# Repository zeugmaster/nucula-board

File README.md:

# Nucula Board

An ESP32-C3 hardware prototype with USB-C, battery charging, PN7160 NFC,
an SSD1309 OLED interface, and a detachable I²C keyboard section.

**Current production files: [production-2026-10-09-package.zip](manufacturing/production-2026-10-09-package.zip).**
The current board preserves rev-A NFC copper, matching values and placement,
including its small vias, filled/capped fabrication and JLC04161H-3313 stackup.
It retains the corrected display mapping, USB isolation redesign, MINI-1 module,
six M2 holes, inward battery connector and rounded cable notch.
[Production instructions and validation scope](docs/production-release.md).
All previous October packages are superseded for this order. Revised USB/display
operation and the new NFC substitutes still require bench validation. See the
stock-substitution qualification included in this release.

## Open the design

Clone this repository and open `nucula-v2.kicad_pro` in **KiCad 10** with its
standard symbol, footprint and 3D libraries installed. Project-specific libraries
use relative paths. The project filenames retain the hardware revision name
`nucula-v2`; the GitHub repository is `nucula-board`.

```sh
git clone https://github.com/zeugmaster/nucula-board.git
cd nucula-board
python3 tools/check_schematic.py
```

The check requires Python 3 and KiCad CLI. See [validation and repository
notes](docs/publication.md) for other checks, dependencies and historical inputs.

## Hardware and documentation

The five-sheet schematic contains the ESP32-C3-MINI-1-H4X, native USB-C data,
a 100 mA single-cell Li-ion charger with JST-SH connector, USB/battery supply
selection, a 3.31 V buck rail, and boot/reset/voltage supervision. It is adapted
from Olimex ESP32-C3-DevKit-Lipo **revision C**. It now includes the PN7160 NFC
controller and antenna matching tree, SSD1309 OLED glass driver/boost supply,
and a detachable PCF8574T keyboard section. The four-layer PCB is placed and
routed, with all components on top and the NFC circuitry inside the coil.

- [M2 mounting-hole positions, clearances and validation](docs/mounting-holes.md)
- [MINI-1 compatibility, pin map, antenna fit and firmware requirements](docs/esp32-mini.md)
- [Completed PCB layout, layer drawings and validation](docs/pcb-layout.md)
- [Rev-A display correction, backfeed investigation and measurements](docs/bringup/rev-b-display-and-usb.md)
- [Rev-A bench procedure with enlarged probe-pad map (PDF)](docs/bringup/rev-A-usb-bench-guide.pdf)
- [Routing repair, before/after comparison and geometry audit](docs/routing-review.md)
- [Standard manufacturing package and order settings](docs/manufacturing-release.md)
- [Current prototype manufacturing ZIP](manufacturing/production-2026-10-09-package.zip)
- [Side-entry battery connector selection, polarity and assembly instructions](docs/battery-connector.md)
- [Circuit simulation screening, findings and model limits](docs/simulation/README.md)
- [Schematic PDF](docs/schematic.pdf)
- [Design choices, datasheets and outstanding hardware limits](docs/power-design.md)
- [NFC, OLED, I²C pin map and breakaway keyboard design](docs/peripherals-design.md)
- [35 mm keyboard breakaway geometry and separation instructions](docs/keyboard-breakaway.md)
- [40 mm NFC coil, calculated matching values and prototype tuning guide](docs/nfc-antenna.md)
- [Selected crystal, capacitor calculations and confirmed prototype interfaces](docs/component-refinements.md)
- [Five-board assembly audit and historical sourcing notes](docs/assembly-readiness.md)
- [Manufacturing simplification and ribbon-clearance changes](docs/standard-fabrication.md)
- [BOM](docs/bom.csv) and [verification results](docs/verification.json)
- [Project library sources and licenses](libraries/README.md)

Battery target: approximately 400 mAh, protected single-cell Li-ion/LiPo,
3.7 V nominal / 4.2 V full. J2 is **JST SH SM02B-SRSS-TB(LF)(SN), C160402**:
**side entry, 1.00 mm pitch, 2.95 mm mated height**, opening toward the left
edge. Use an **SHR-02V-S-B** lead, pin 1 positive and pin 2 ground; the old
PH plug no longer fits. Charging remains 100 mA (0.25C at 400 mAh).
Battery operation remains optional. The user accepts intermittent peaks above
the connector's 1 A rating; no current limit is added. Runtime, discharge
qualification and low-battery improvements remain deferred.
[Connector dimensions, current assumption and assembly details](docs/battery-connector.md).
The intended USB source is a dedicated **5 V / at least 1.5 A** supply; the
steady-state planning budget is about 1.10 A including charging. Startup/inrush
must be tested; operation from arbitrary computer hosts is not qualified.

Run `python3 tools/check_schematic.py` to repeat ERC, connectivity, pad/model and
voltage checks. KiCad's standard symbols, footprints and 3D models are required;
`KICAD_CLI` and `KICAD_SHARE` can override their locations. The project-specific
parts and the ESP32 STEP model are included with relative paths in `libraries/`.
The optional PN7160 3D model is omitted because its terms prohibit redistribution;
its symbol and electrical footprint are included.
All 130 schematic components have assigned footprints; the PCB also includes
two breakaway footprints and six mechanical mounting holes. A1 is a reusable four-turn
40 × 40 mm PCB coil with its bottom return and copper keepout included. The NFC
tree retains the rev-A values, 0805 tuning pads and TX isolation links; no retuning
change was made for this release. [A separate bare-coil coupon](prototypes/nfc-antenna/nfc-antenna.kicad_pro)
is available for fabrication and measurement. The OLED now uses the **24-contact
CON24 pinout** in the reference breakout schematic, superseding the earlier
26-contact assumption. DS1 is a Hirose FH12A-24S-0.5SH(55), 0.5 mm top-contact socket (C506794).
[Pinout and regression checks](docs/oled24/README.md) cover all 24 connections.
In the mounted PCB top view, panel pin 1 is left and pin 24 right:
**panel pin n connects to Hirose socket pad 25−n**. The manufacturer footprint
numbering is preserved; the mounted-contact checker now verifies this distinction.
The target panel has ribbon marking **NFP1309-02Y**: 2.4-inch COG,
0.50 mm pitch, 0.30 mm flex, contacts on the emitting face. In its confirmed
mounted position the tip contacts face away from the PCB. The
[top-contact update and checks](docs/oled24/top-contact.md) cover the new lands,
paste apertures and 0.20 mm placement adjustment. The display and external keypad are excluded
from the assembly BOM; DS1 purchases the socket only.
See the library notes for unavailable models.

The shared I²C bus runs at 100 kHz: PN7160 `0x28`, SSD1309 `0x3C`, PCF8574T `0x20`.
PCF8574T is an eight-bit I/O expander; no bus multiplexer is needed.
Its SOIC-16W_7.5x10.3mm_P1.27mm footprint matches the earlier BOM.
J3 is the user-fitted, DNP nine-pin keyboard header: **pins 1 and 9 are NC;
pins 2–8 connect to P0–P6**, preserving the early board's seven-line order.
[Keypad pinout and scanning notes](docs/keyboard-interface.md).
J4/J5 are optional DNP
five-pin headers for reconnecting the keyboard section after separation.

Y1 is now NDK NX2016SA-27.12MHZ-EXS00A-CS06346 (JLCPCB C3008209),
2.0 × 1.6 mm, with calculated 12 pF / 15 pF load-capacitor starts. Power
capacitor ordering codes and larger bulk footprints are selected using archived
manufacturer DC-bias curves. Run `python3 tools/check_component_choices.py` to
reproduce those estimates. RF tuning, oscillator qualification and power
measurements remain prototype bring-up work. **Placement and routing are complete**
for the agreed USB-powered prototype. Native PCB DRC has zero errors and zero unconnected or schematic-parity findings.
The 33 reviewed warnings are cosmetic. The exact NFC comparison covers 43
footprints and 366 routing objects. Strict routing findings inherited from the
proven NFC layout are disclosed and preserved; there are no new routing findings.
The 261 preflight and 57 USB SPICE cases were rerun, plus the independent NFC
numerical cross-check. [Full scope](docs/production-release.md).

Git tracks design files, project libraries and documentation. Local editor state,
lock files, automatic backups and KiCad's `.history` are ignored.

Manufacturing files now target five bare four-layer boards, nominal 1.6 mm,
black mask, white legend and ENIG using the rev-A JLC04161H-3313 stackup.
All small plated round holes require epoxy filling and copper capping; the
restored NFC uses 0.20 mm drill / 0.45 mm land and 0.30 / 0.60 mm vias.
There is no controlled-impedance requirement. The October package includes
119-part placements, stencil data, assembly drawings, and JLCPCB BOM/CPL inputs.
Its BOM includes the USB redesign and side-entry J2. J6 direct battery wire pads
are etched copper and need no purchased component.
[Manufacturing changes and validation](docs/standard-fabrication.md).

The [JLCPCB r2 archive](manufacturing/jlcpcb-2026-09-21-r2-package.zip) records
the previously submitted board and remains unchanged. Its order settings and
placements belong to that earlier design. Use the October prototype package
for the revised design; USB reconnection, ESD and display operation still need
validation on revised hardware.

## License and attribution

The hardware design is distributed under [CERN-OHL-S-2.0](LICENSE), retaining
the attribution and license of the Olimex ESP32-C3-DevKit-Lipo revision C design
from which the power section was adapted. Third-party library assets and
reference documents retain their own terms; see [library attribution](libraries/README.md)
and [LICENSES](LICENSES/). These notices do not grant additional rights to
third-party material. Firmware is not included in this repository.

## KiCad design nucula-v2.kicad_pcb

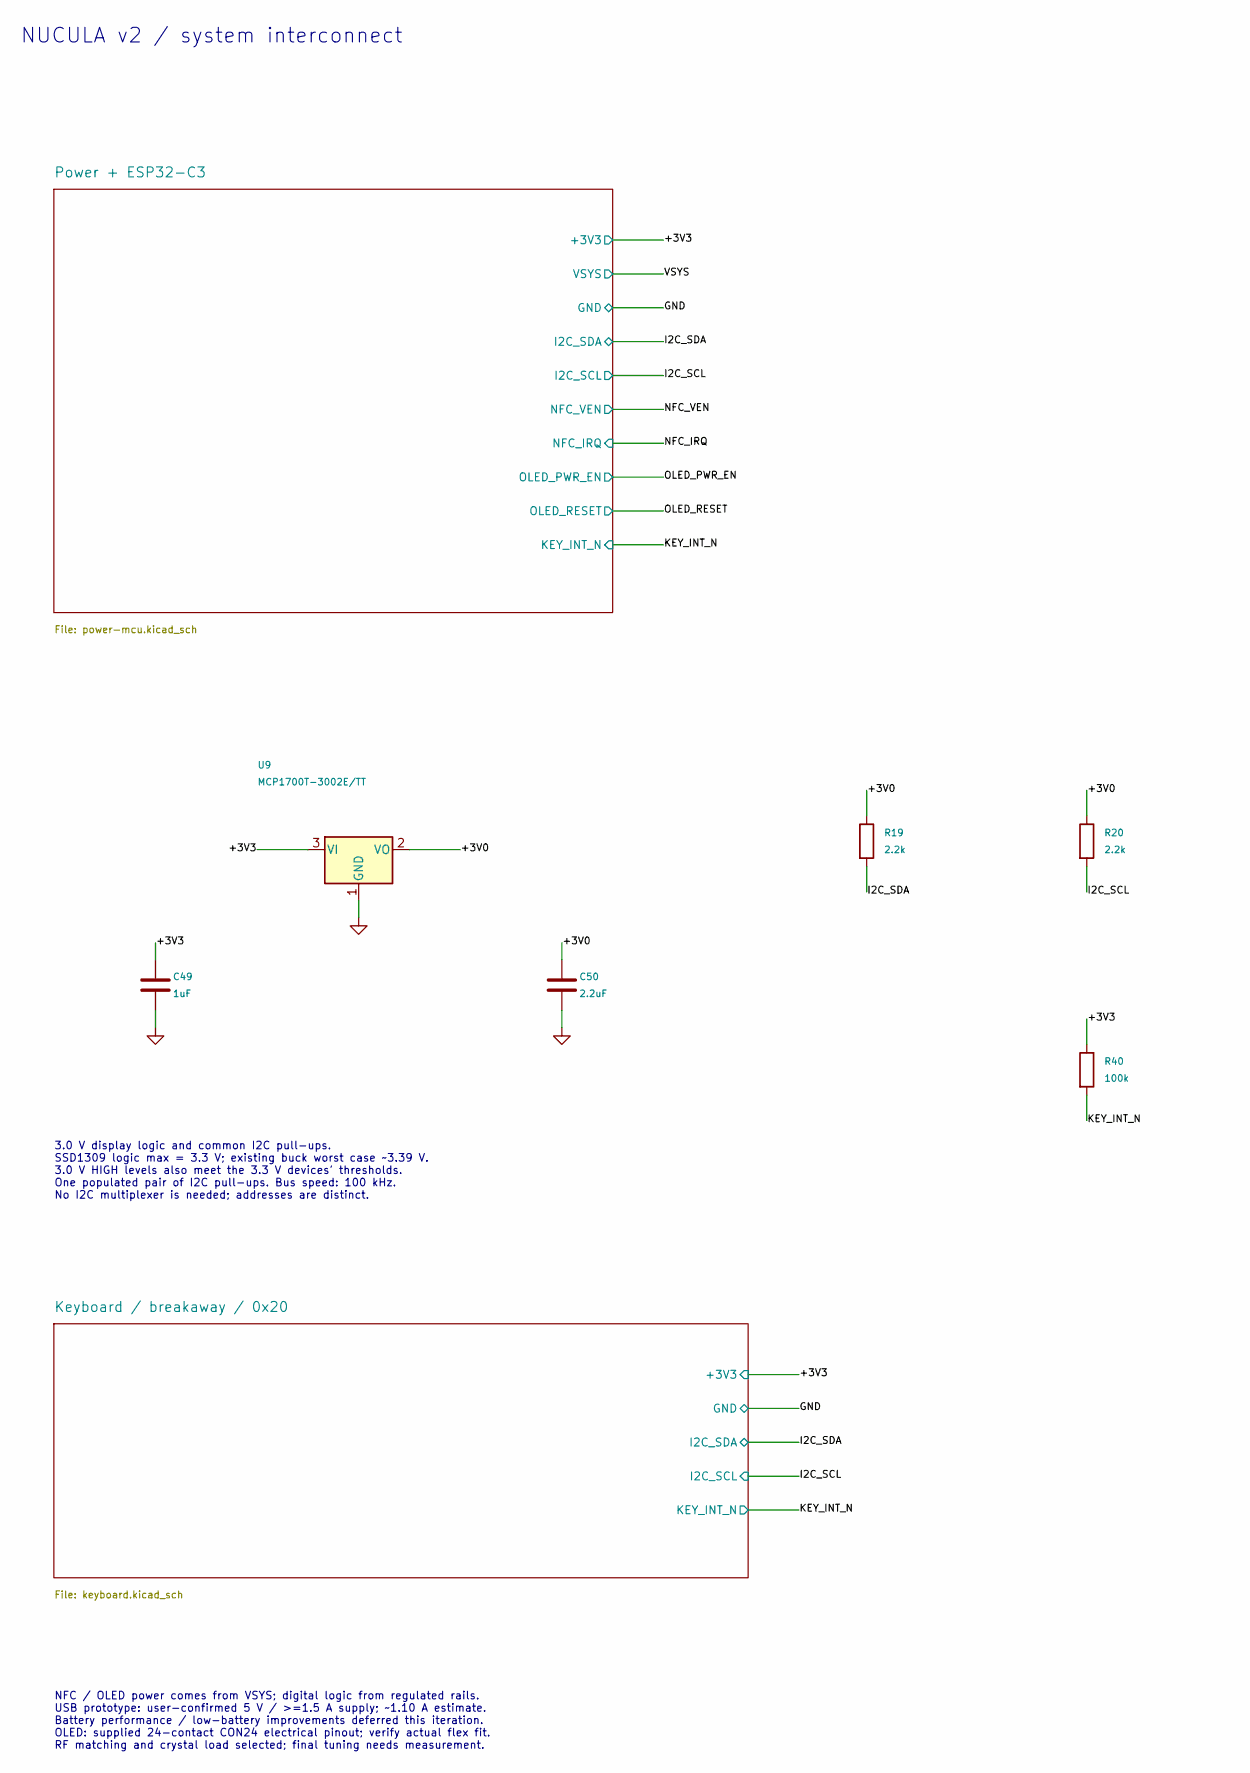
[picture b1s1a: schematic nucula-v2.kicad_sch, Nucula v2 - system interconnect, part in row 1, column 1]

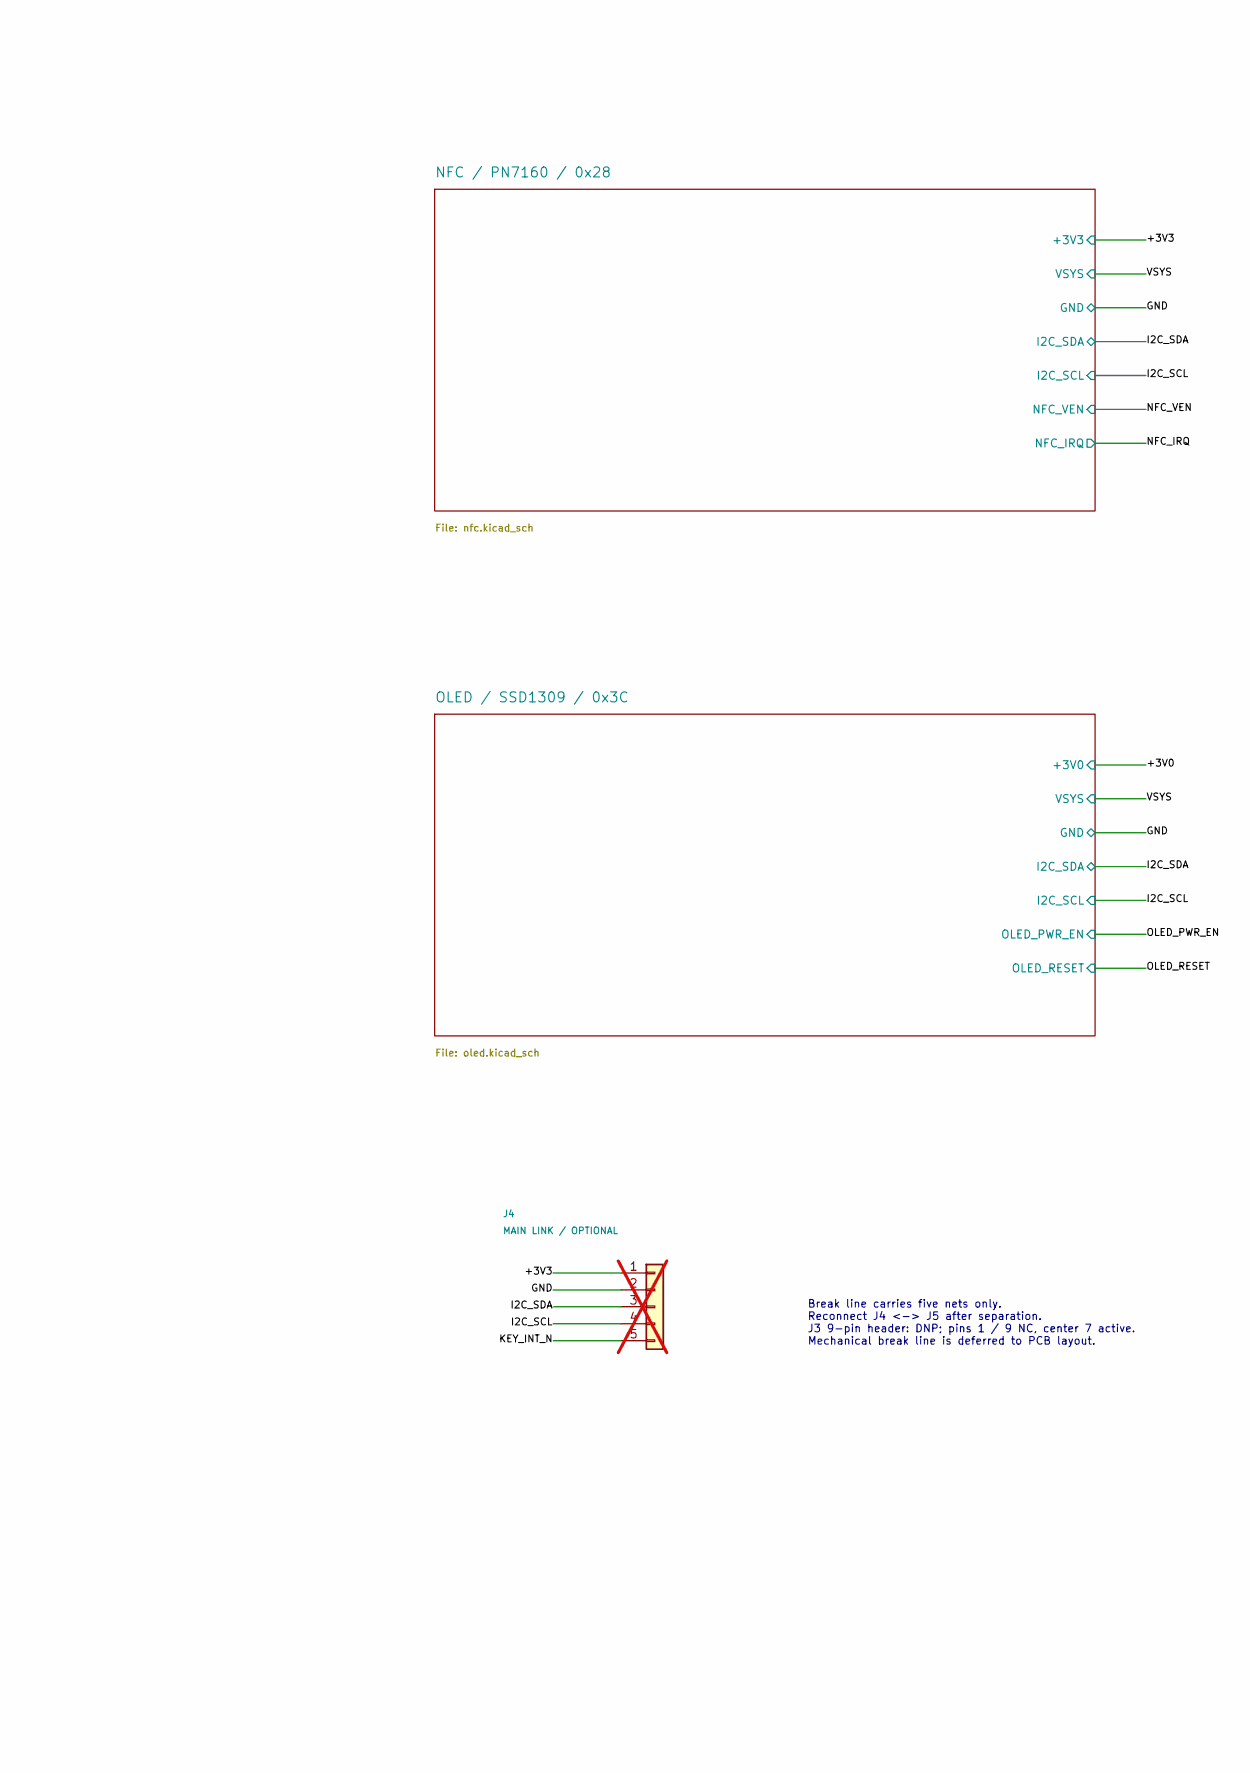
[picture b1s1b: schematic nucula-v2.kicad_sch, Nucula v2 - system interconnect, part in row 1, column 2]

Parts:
C49: 1uF; C_0805_2012Metric; Voltage 50 V; Tolerance 10%; MPN CL21B105KBFNNNE; LCSC C28323
C50: 2.2uF; C_0805_2012Metric; Voltage 25 V; Tolerance 10%; MPN CL21B225KAFNNNE; LCSC C19110
J4: MAIN LINK / OPTIONAL; PinHeader_1x05_P2.54mm_Vertical; not fitted
R19, R20: 2.2k; R_0603_1608Metric; Tolerance 1%; Rating 0.1 W; MPN 0603WAF2201T5E; LCSC C4190
R40: 100k; R_0603_1608Metric; Tolerance 1%; Rating 0.1 W; MPN 0603WAF1003T5E; LCSC C25803
U9: MCP1700T-3002E/TT; SOT-23; MPN MCP1700T-3002E/TT; LCSC C62244

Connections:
/+3V0: C50.1, R19.1, R20.1, U9.2 (VO); also elsewhere on the board
/+3V3: C49.1, J4.1, R40.1, U9.3 (VI); also elsewhere on the board
/I2C_SCL: J4.4, R20.2; also elsewhere on the board
/I2C_SDA: J4.3, R19.2; also elsewhere on the board
/KEY_INT_N: J4.5, R40.2; also elsewhere on the board
GND: C49.2, C50.2, J4.2, U9.1 (GND); also elsewhere on the board

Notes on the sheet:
NUCULA v2 / system interconnect
3.0 V display logic and common I2C pull-ups. SSD1309 logic max = 3.3 V; existing buck worst case ~3.39 V. 3.0 V HIGH levels also meet the 3.3 V devices' thresholds. One populated pair of I2C pull-ups. Bus speed: 100 kHz. No I2C multiplexer is needed; addresses are distinct.
Break line carries five nets only. Reconnect J4 <-> J5 after separation. J3 9-pin header: DNP; pins 1 / 9 NC, center 7 active. Mechanical break line is deferred to PCB layout.
NFC / OLED power comes from VSYS; digital logic from regulated rails. USB prototype: user-confirmed 5 V / >=1.5 A supply; ~1.10 A estimate. Battery performance / low-battery improvements deferred this iteration. OLED: supplied 24-contact CON24 electrical pinout; verify actual flex fit. RF matching 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

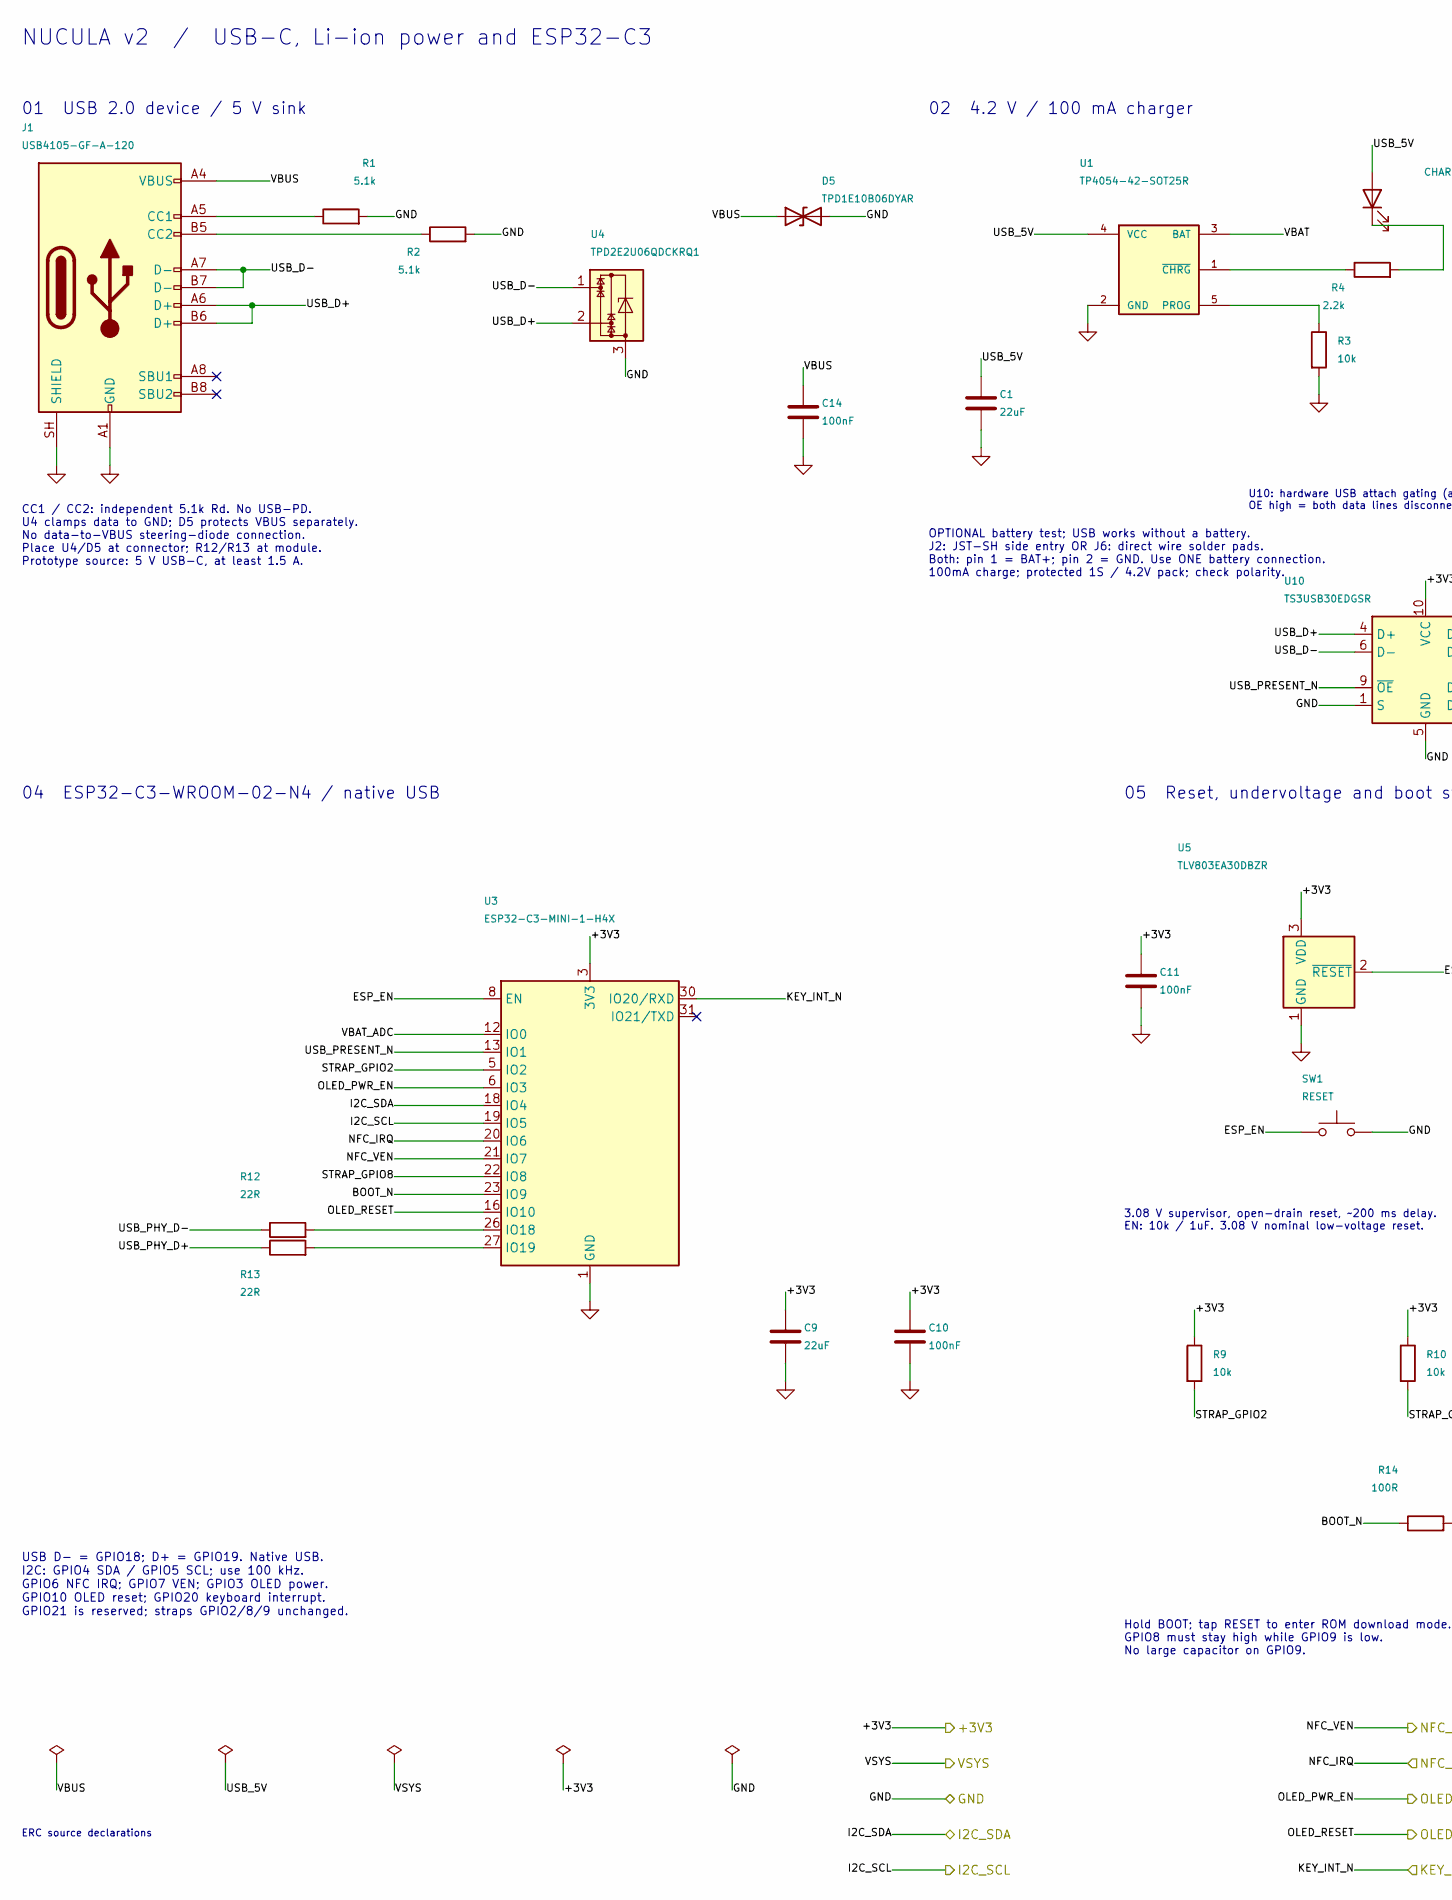
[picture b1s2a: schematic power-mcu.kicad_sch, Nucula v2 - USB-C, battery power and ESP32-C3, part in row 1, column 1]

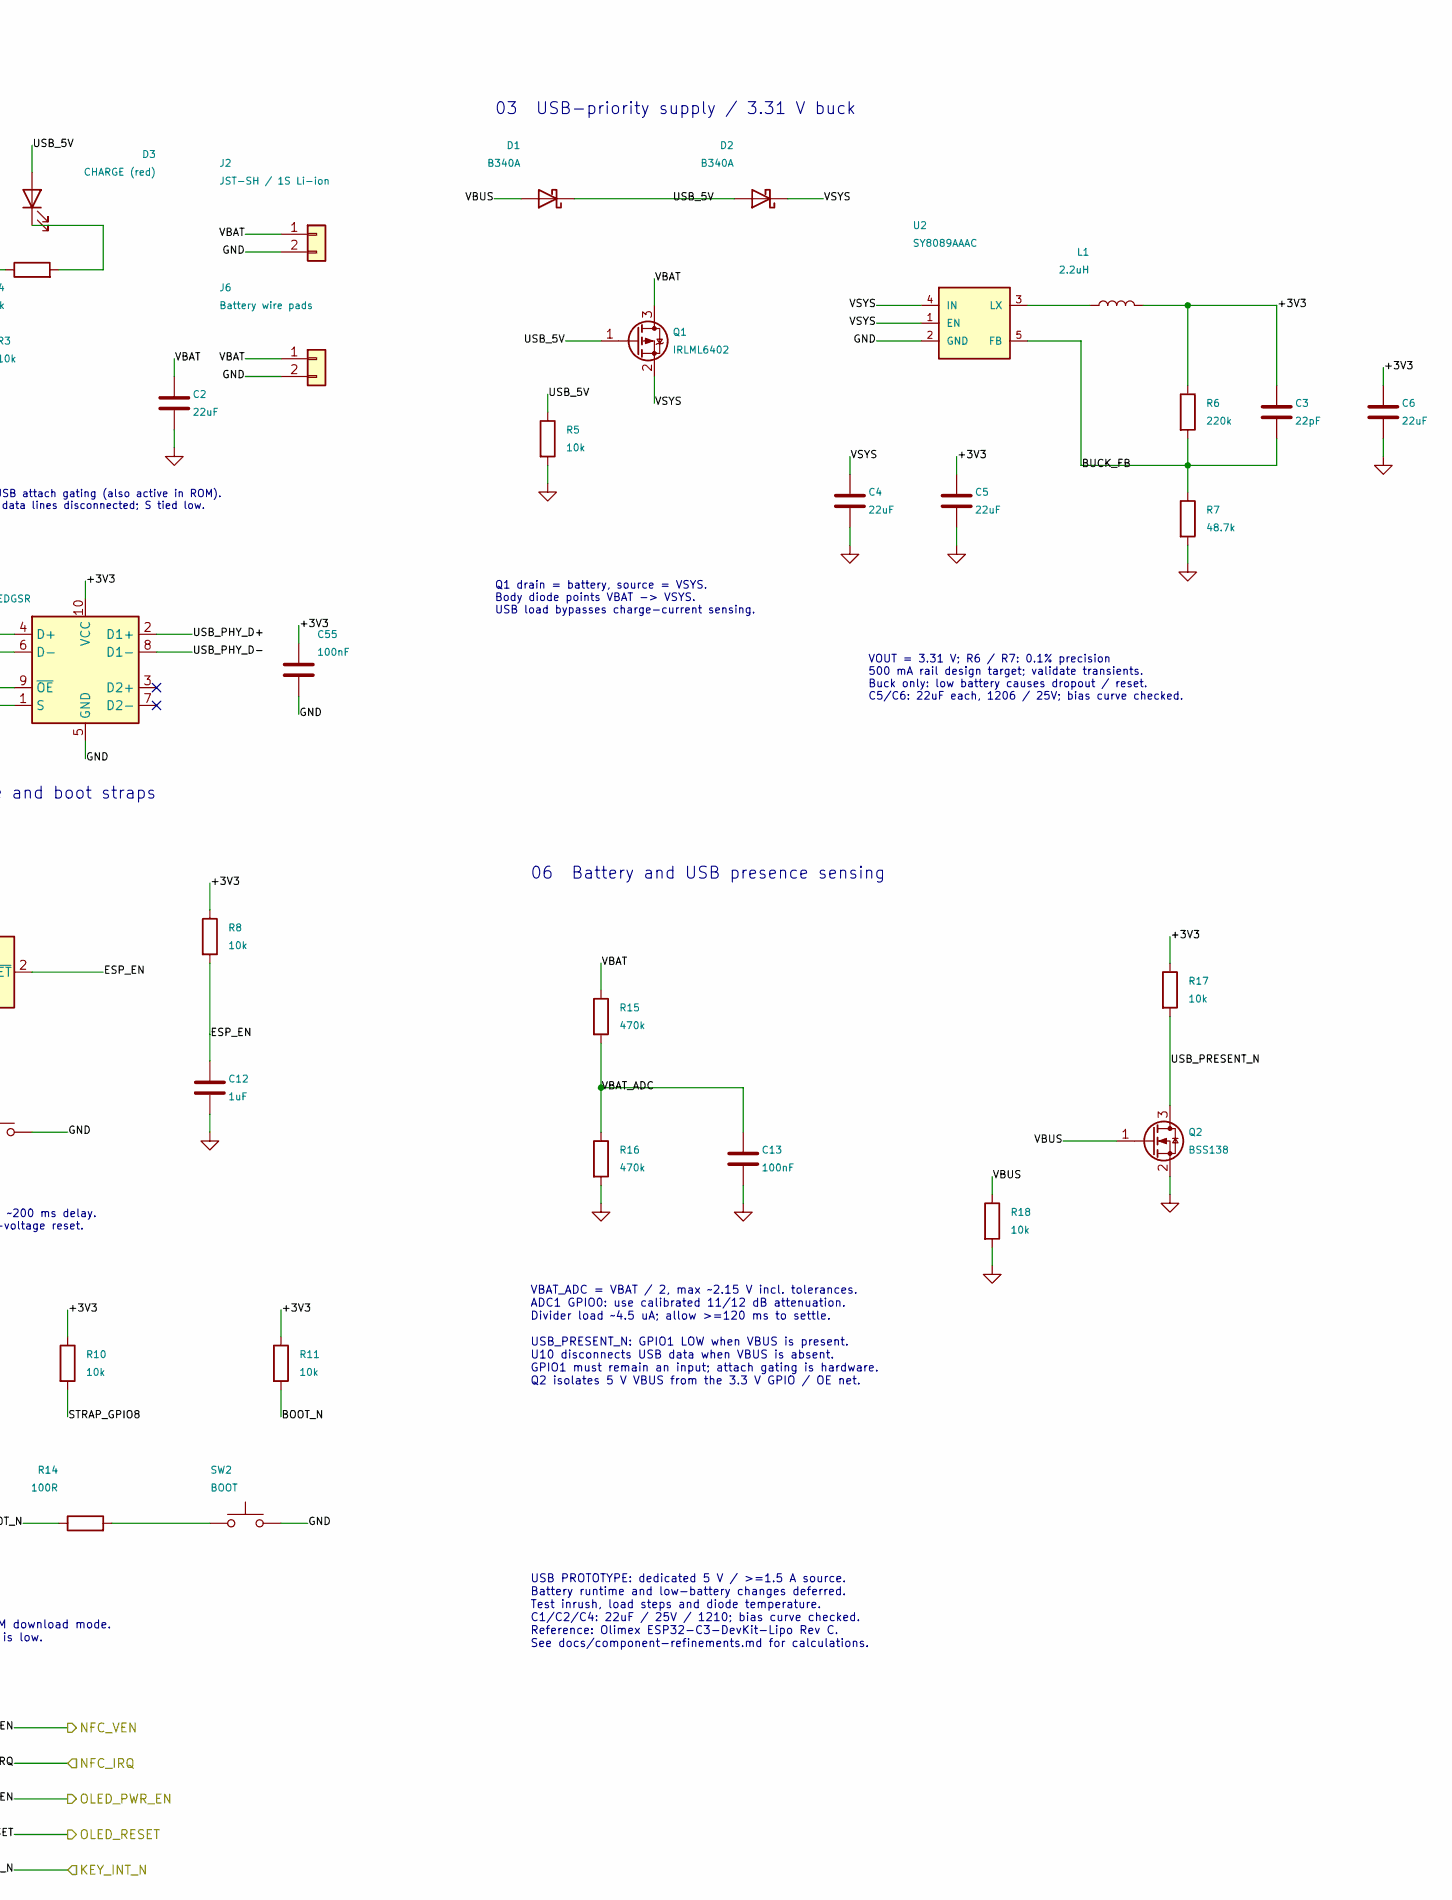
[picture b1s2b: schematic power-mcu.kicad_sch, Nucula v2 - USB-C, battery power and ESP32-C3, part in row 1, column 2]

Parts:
C1, C2, C4: 22uF; C_1210_3225Metric; Voltage 25 V; Tolerance 10%; MPN CL32B226KAJNNNE; LCSC C309062
C3: 22pF; C_0603_1608Metric; Voltage 50 V; Tolerance 5%; MPN CL10C220JB8NNNC; LCSC C1653
C5, C6, C9: 22uF; C_1206_3216Metric; Voltage 25 V; Tolerance 10%; MPN CL31A226KAHNNNE; LCSC C12891
C10, C11, C13, C14, C55: 100nF; C_0603_1608Metric; Voltage 50 V; Tolerance 10%; MPN CL10B104KB8NNNL; LCSC C913912
C12: 1uF; C_0603_1608Metric; Voltage 25 V; Tolerance 10%; MPN CL10B105KA8NNNC; LCSC C29936
D1, D2: B340A; D_SMA; Rating 3 A / 40 V; SMA; layout thermal deratin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; MPN B340A-13-F; LCSC C85098
D3: CHARGE (red); LED_0603_1608Metric; MPN KT-0603R; LCSC C2286
D5: TPD1E10B06DYAR; D_SOD-523; MPN TPD1E10B06DYAR; LCSC C3712135
J1: USB4105-GF-A-120; USB_C_GCT_USB4105_16P_Standard; MPN USB4105-GF-A-120; LCSC C5184243
J2: JST-SH / 1S Li-ion; JST_SH_SM02B-SRSS-TB_1x02-1MP_P1.00mm_Horizontal; MPN SM02B-SRSS-TB(LF)(SN); LCSC C160402
J6: Battery wire pads; Battery_Lead_SolderPads_2x2.2x2.5mm_P3.4mm
L1: 2.2uH; L_Taiyo-Yuden_NR-30xx; Rating Isat >=1.48 A, Irms >=1.5 A; 2.2uH +/-2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; MPN LSXND3030QKT2R2MNG; LCSC C6980123
Q1: IRLML6402; SOT-23; MPN IRLML6402TRPBF; LCSC C2593
Q2: BSS138; SOT-23; MPN BSS138; LCSC C52895
R1, R2: 5.1k; R_0603_1608Metric; Tolerance 1%; Rating 0.1 W; MPN 0603WAF5101T5E; LCSC C23186
R3, R5, R8, R9, R10, R11, R17, R18: 10k; R_0603_1608Metric; Tolerance 1%; Rating 0.1 W; MPN 0603WAF1002T5E; LCSC C25804
R4: 2.2k; R_0603_1608Metric; Tolerance 1%; Rating 0.1 W; MPN 0603WAF2201T5E; LCSC C4190
R6: 220k; R_0603_1608Metric; Tolerance 0.1%; Rating 0.1 W; MPN RT0603BRD07220KL; LCSC C861231
R7: 48.7k; R_0603_1608Metric; Tolerance 0.1%; Rating 0.1 W; MPN RT0603BRD0748K7L; LCSC C861429
R12, R13: 22R; R_0603_1608Metric; Tolerance 1%; Rating 0.1 W; MPN 0603WAF220JT5E; LCSC C23345
R14: 100R; R_0603_1608Metric; Tolerance 1%; Rating 0.1 W; MPN 0603WAF1000T5E; LCSC C22775
R15, R16: 470k; R_0603_1608Metric; Tolerance 1%; Rating 0.1 W; MPN 0603WAF4703T5E; LCSC C23178
SW1: RESET; SW_SPST_B3U-1000P; MPN B3U-1000P; LCSC C231329
SW2: BOOT; SW_SPST_B3U-1000P; MPN B3U-1000P; LCSC C231329
U1: TP4054-42-SOT25R; SOT-23-5; MPN TP4054-42-SOT25R; LCSC C32574
U2: SY8089AAAC; SOT-23-5; MPN SY8089AAAC; LCSC C78988
U3: ESP32-C3-MINI-1-H4X; ESP32-C3-MINI-1-H4X_NoEPADSolder; MPN ESP32-C3-MINI-1-H4X; LCSC C41349510
U4: TPD2E2U06QDCKRQ1; SOT-323_SC-70; MPN TPD2E2U06QDCKRQ1; LCSC C915089
U5: TLV803EA30DBZR; SOT-23; MPN TLV803EA30DBZR; LCSC C5218924
U10: TS3USB30EDGSR; TSSOP-10_3x3mm_P0.5mm; MPN TS3USB30EDGSR; LCSC C131998

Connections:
/+3V3: C3.1, C5.1, C6.1, C9.1, C10.1, C11.1, C55.1, L1.2, R6.1, R8.1, R9.1, R10.1, R11.1, R17.1, U3.3 (3V3), U5.3 (VDD), U10.10 (VCC); also elsewhere on the board
/I2C_SCL: U3.19 (IO5); also elsewhere on the board
/I2C_SDA: U3.18 (IO4); also elsewhere on the board
/KEY_INT_N: U3.30 (IO20/RXD); also elsewhere on the board
/NFC_IRQ: U3.20 (IO6); also elsewhere on the board
/NFC_VEN: U3.21 (IO7); also elsewhere on the board
/OLED_PWR_EN: U3.6 (IO3); also elsewhere on the board
/OLED_RESET: U3.16 (IO10); also elsewhere on the board
/Power + ESP32-C3/BOOT_N: R11.2, R14.1, U3.23 (IO9)
/Power + ESP32-C3/BUCK_FB: C3.2, R6.2, R7.1, U2.5 (FB)
/Power + ESP32-C3/ESP_EN: C12.1, R8.2, SW1.1, U3.8 (EN), U5.2 (~RESET)
/Power + ESP32-C3/STRAP_GPIO2: R9.2, U3.5 (IO2)
/Power + ESP32-C3/STRAP_GPIO8: R10.2, U3.22 (IO8)
/Power + ESP32-C3/USB_5V: C1.1, D1.1 (K), D2.2 (A), D3.2 (A), Q1.1 (G), R5.1, U1.4 (VCC)
/Power + ESP32-C3/USB_D+: J1.A6 (D+), J1.B6 (D+), U4.2, U10.4 (D+)
/Power + ESP32-C3/USB_D-: J1.A7 (D-), J1.B7 (D-), U4.1, U10.6 (D-)
/Power + ESP32-C3/USB_PHY_D+: R13.1, U10.2 (D1+)
/Power + ESP32-C3/USB_PHY_D-: R12.1, U10.8 (D1-)
/Power + ESP32-C3/USB_PRESENT_N: Q2.3 (D), R17.2, U3.13 (IO1), U10.9 (~OE)
/Power + ESP32-C3/VBAT: C2.1, J2.1, J6.1, Q1.3 (D), R15.1, U1.3 (BAT)
/Power + ESP32-C3/VBAT_ADC: C13.1, R15.2, R16.1, U3.12 (IO0)
/Power + ESP32-C3/VBUS: C14.1, D1.2 (A), D5.1 (A1), J1.A4 (VBUS), J1.A9 (VBUS), J1.B4 (VBUS), J1.B9 (VBUS), Q2.1 (G), R18.1
/VSYS: C4.1, D2.1 (K), Q1.2 (S), U2.1 (EN), U2.4 (IN); also elsewhere on the board
GND: C1.2, C2.2, C4.2, C5.2, C6.2, C9.2, C10.2, C11.2, C12.2, C13.2, C14.2, C55.2, D5.2 (A2), J1.A1 (GND), J1.A12 (GND), J1.B1 (GND), J1.B12 (GND), J1.SH (SHIELD), J2.2, J6.2, Q2.2 (S), R1.2, R2.2, R3.2, R5.2, R7.2, R16.2, R18.2, SW1.2, SW2.2, U1.2 (GND), U2.2 (GND), U3.1 (GND), U3.2 (GND), U3.11 (GND), U3.14 (GND), U3.36 (GND), U3.37 (GND), U3.38 (GND), U3.39 (GND), U3.40 (GND), U3.41 (GND), U3.42 (GND), U3.43 (GND), U3.44 (GND), U3.45 (GND), U3.46 (GND), U3.47 (GND), U3.48 (GND), U3.49 (GND), U3.50 (GND), U3.51 (GND), U3.52 (GND), U3.53 (GND), U4.3, U5.1 (GND), U10.1 (S), U10.5 (GND); also elsewhere on the board
unnamed: D3.1 (K), R4.2
unnamed: J1.A5 (CC1), R1.1
unnamed: J1.B5 (CC2), R2.1
unnamed: R14.2, SW2.1
unnamed: R3.1, U1.5 (PROG)
unnamed: R4.1, U1.1 (~CHRG)
unnamed: L1.1, U2.3 (LX)
unnamed: R12.2, U3.26 (IO18)
unnamed: R13.2, U3.27 (IO19)

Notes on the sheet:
NUCULA v2 / USB-C, Li-ion power and ESP32-C3
01 USB 2.0 device / 5 V sink
CC1 / CC2: independent 5.1k Rd. No USB-PD. U4 clamps data to GND; D5 protects VBUS separately. No data-to-VBUS steering-diode connection. Place U4/D5 at connector; R12/R13 at module. Prototype source: 5 V USB-C, at least 1.5 A.
02 4.2 V / 100 mA charger
OPTIONAL battery test; USB works without a battery. J2: JST-SH side entry OR J6: direct wire solder pads. Both: pin 1 = BAT+; pin 2 = GND. Use ONE battery connection. 100mA charge; protected 1S / 4.2V pack; check polarity.
03 USB-priority supply / 3.31 V buck
Q1 drain = battery, source = VSYS. Body diode points VBAT -> VSYS. USB load bypasses charge-current sensing.
VOUT = 3.31 V; R6 / R7: 0.1% precision 500 mA rail design target; validate transients. Buck only: low battery causes dropout / reset. C5/C6: 22uF each, 1206 / 25V; bias curve checked.
04 ESP32-C3-WROOM-02-N4 / native USB
USB D- = GPIO18; D+ = GPIO19. Native USB. I2C: GPIO4 SDA / GPIO5 SCL; use 100 kHz. GPIO6 NFC IRQ; GPIO7 VEN; GPIO3 OLED power. GPIO10 OLED reset; GPIO20 keyboard interrupt. GPIO21 is reserved; straps GPIO2/8/9 unchanged.
05 Reset, undervoltage and boot straps
3.08 V supervisor, open-drain reset, ~200 ms delay. EN: 10k / 1uF. 3.08 V nominal low-voltage reset.
Hold BOOT; tap RESET to enter ROM download mode. GPIO8 must stay high while GPIO9 is low. No large capacitor on GPIO9.
06 Battery and USB presence sensing
VBAT_ADC = VBAT / 2, max ~2.15 V incl. tolerances. ADC1 GPIO0: use calibrated 11/12 dB attenuation. Divider load ~4.5 uA; allow >=120 ms to settle. USB_PRESENT_N: GPIO1 LOW when VBUS is present. U10 disconnects USB data when VBUS is absent. GPIO1 must remain an input; attach gating is hardware. Q2 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
USB PROTOTYPE: dedicated 5 V / >=1.5 A source. Battery runtime and low-battery changes deferred. Test inrush, load steps and diode temperature. C1/C2/C4: 22uF / 25V / 1210; bias curve checked. Reference: Olimex ESP32-C3-DevKit-Lipo Rev C. See docs/component-refinements.md for calculations.
ERC source declarations
U10: hardware USB attach gating (also active in ROM). OE high = both data lines disconnected; S tied low.
